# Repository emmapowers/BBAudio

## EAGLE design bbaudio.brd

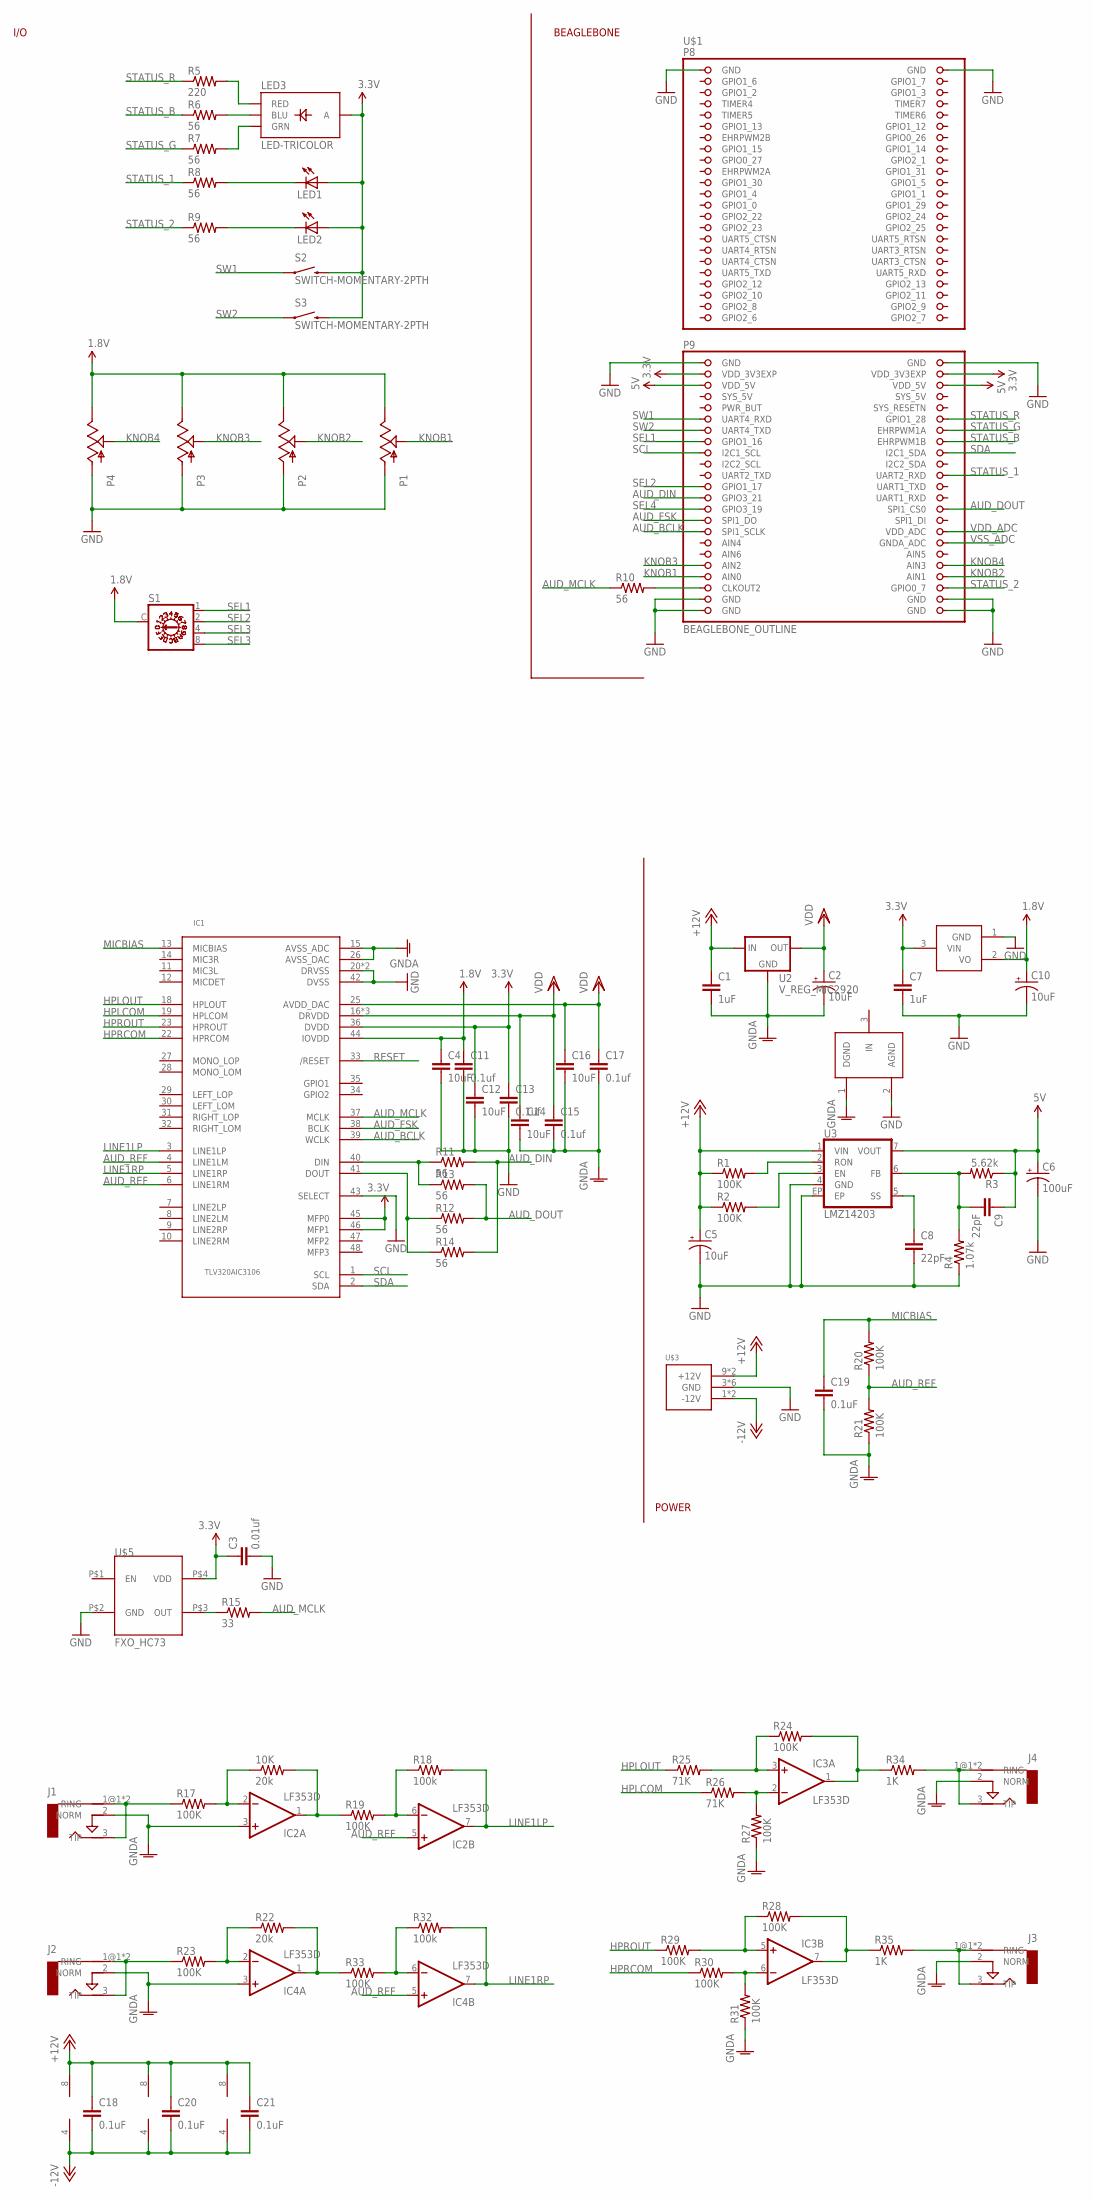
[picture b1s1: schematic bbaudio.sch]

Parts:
10K: 20k; 0603-RES
C1, C7: 1uF; C0603
C2, C5, C10: 10uF; EIA3216
C3: 0.01uf; C0603
C4, C12, C14, C16: 10uF; C0603
C6: 100uF; EIA3216
C8, C9: 22pF; C0603
C11, C13, C15, C17: 0.1uf; C0603
C18, C19, C20, C21: 0.1uF; C0603
IC1: TLV320AIC3106; QFN48
IC2, IC3, IC4: LF353D; SO08
J1, J2, J3, J4: AUDIO-JACKERTHENVAR; ERTHENVAR-JACK
LED1, LED2: LED-FKIT-1206; FKIT-LED-1206
LED3: LED-TRICOLOR; LED-TRICOLOR-SMD
P1, P2, P3, P4: SPARKFUN_POTPDB12; SPARKFUN_PDB12
R1, R2, R17, R19, R20, R21, R23, R24, R27, R28, R29, R30, R31, R33: 100K; 0603-RES
R3: 5.62k; 0603-RES
R4: 1.07k; 0603-RES
R5: 220; 0603-RES
R6, R7, R8, R9, R10, R11, R12, R13, R14: 56; 0603-RES
R15: 33; 0603-RES
R18, R32: 100k; 0603-RES
R22: 20k; 0603-RES
R25, R26: 71K; 0603-RES
R34, R35: 1K; 0603-RES
S1: P103
S2, S3: SWITCH-MOMENTARY-2PTH; TACTILE-PTH
U2: V_REG_MIC2920; SOT223
U3: LMZ14203; TO-PMOD-7
U4: VREG; SOT23-3
U$1: BEAGLEBONE_OUTLINE; BEAGLEBONE_SHIELD
U$3: POWER_SIMPLE10; POWER_10
U$5: FXO_HC73; 4PIN
U$11: GND_CONNECT

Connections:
1.8V: C4.1, C10.A (+), C11.1, IC1.44 (IOVDD), P1.3 (E), P2.3 (E), P3.3 (E), P4.3 (E), S1.C, U4.2 (VO)
3.3V: C3.1, C7.1, C12.1, C13.1, IC1.36 (DVDD), IC1.45 (MFP0), IC1.46 (MFP1), LED1.A, LED2.A, LED3.A, S2.3 (2), S3.3 (2), U4.3 (VIN), U$1.49 (VDD_3V3EXP), U$1.50 (VDD_3V3EXP), U$5.P$4 (VDD)
5V: C6.A (+), C9.1, R3.1, U3.7 (VOUT), U$1.51 (VDD_5V), U$1.52 (VDD_5V)
+12V: C1.1, C5.A (+), C18.1, C20.1, C21.1, IC2.8 (V+), IC3.8 (V+), IC4.8 (V+), R1.1, R2.1, U2.1 (IN), U3.1 (VIN), U$3.9 (+12V), U$3.10 (+12V)
-12V: C18.2, C20.2, C21.2, IC2.4 (V-), IC3.4 (V-), IC4.4 (V-), U$3.1 (-12V), U$3.2 (-12V)
AUD_BCLK: IC1.39 (WCLK), U$1.77 (SPI1_SCLK)
AUD_DIN: R11.2, R14.2, U$1.71 (GPIO3_21)
AUD_DOUT: R12.2, R13.2, U$1.74 (SPI1_CS0)
AUD_FSK: IC1.38 (BCLK), U$1.75 (SPI1_DO)
AUD_MCLK: IC1.37 (MCLK), R10.1, R15.2
AUD_REF: IC1.4 (LINE1LM), IC1.6 (LINE1RM), IC2.5 (+IN), IC4.5 (+IN), R20.1, R21.2
GND: C3.2, C4.2, C5.C (-), C6.C (-), C7.2, C8.2, C10.C (-), C11.2, C12.2, C13.2, IC1.20 (DRVSS), IC1.21 (DRVSS), IC1.42 (DVSS), IC1.43 (SELECT), P1.1 (A), P2.1 (A), P3.1 (A), P4.1 (A), R4.1, U3.4 (GND), U3.EP, U4.1 (GND), U$1.1 (GND), U$1.2 (GND), U$1.47 (GND), U$1.48 (GND), U$1.89 (GND), U$1.90 (GND), U$1.91 (GND), U$1.92 (GND), U$3.3 (GND), U$3.4 (GND), U$3.5 (GND), U$3.6 (GND), U$3.7 (GND), U$3.8 (GND), U$5.P$2 (GND), U$11.2 (AGND)
GNDA: C1.2, C2.C (-), C14.2, C15.2, C16.2, C17.2, C19.2, IC1.15 (AVSS_ADC), IC1.26 (AVSS_DAC), IC2.3 (+IN), IC4.3 (+IN), J1.2 (NORM), J2.2 (NORM), J3.2 (NORM), J4.2 (NORM), R21.1, R27.1, R31.1, U2.2 (GND), U$11.1 (DGND)
HPLCOM: IC1.19 (HPLCOM), R26.1
HPLOUT: IC1.18 (HPLOUT), R25.1
HPRCOM: IC1.22 (HPRCOM), R30.1
HPROUT: IC1.23 (HPROUT), R29.1
KNOB1: P1.2 (S), U$1.85 (AIN0)
KNOB2: P2.2 (S), U$1.86 (AIN1)
KNOB3: P3.2 (S), U$1.83 (AIN2)
KNOB4: P4.2 (S), U$1.84 (AIN3)
LINE1LP: IC1.3 (LINE1LP), IC2.7 (OUT), R18.2
LINE1RP: IC1.5 (LINE1RP), IC4.7 (OUT), R32.2
MICBIAS: C19.1, IC1.13 (MICBIAS), R20.2
unnamed: LED3.R (RED), R5.2
unnamed: LED3.B (BLU), R6.2
unnamed: LED3.G (GRN), R7.2
unnamed: LED1.C, R8.2
unnamed: LED2.C, R9.2
unnamed: R1.2, U3.2 (RON)
unnamed: R2.2, U3.3 (EN)
unnamed: C8.1, U3.5 (SS)
unnamed: R10.2, U$1.87 (CLKOUT2)
unnamed: IC1.40 (DIN), R11.1, R13.1
unnamed: IC1.41 (DOUT), R12.1, R14.1
unnamed: R15.1, U$5.P$3 (OUT)
unnamed: C9.2, R3.2, R4.2, U3.6 (FB)
unnamed: 10K.2, IC2.1 (OUT), R19.1
unnamed: IC2.6 (-IN), R18.1, R19.2
unnamed: 10K.1, IC2.2 (-IN), R17.2
unnamed: J1.1@1 (RING), J1.1@2 (RING), J1.3 (TIP), R17.1
unnamed: J2.1@1 (RING), J2.1@2 (RING), J2.3 (TIP), R23.1
unnamed: J4.1@1 (RING), J4.1@2 (RING), J4.3 (TIP), R34.2
unnamed: IC4.2 (-IN), R22.1, R23.2
unnamed: IC4.1 (OUT), R22.2, R33.1
unnamed: IC4.6 (-IN), R32.1, R33.2
unnamed: IC3.1 (OUT), R24.2, R34.1
unnamed: IC3.3 (+IN), R24.1, R25.2
unnamed: IC3.2 (-IN), R26.2, R27.2
unnamed: IC3.7 (OUT), R28.2, R35.1
unnamed: IC3.5 (+IN), R28.1, R29.2
unnamed: IC3.6 (-IN), R30.2, R31.2
unnamed: J3.1@1 (RING), J3.1@2 (RING), J3.3 (TIP), R35.2
RESET: IC1.33 (/RESET)
SCL: IC1.1 (SCL), U$1.63 (I2C1_SCL)
SDA: IC1.2 (SDA), U$1.64 (I2C1_SDA)
SEL1: S1.1, U$1.61 (GPIO1_16)
SEL2: S1.2, U$1.69 (GPIO1_17)
SEL3: S1.4
SEL4: S1.8, U$1.73 (GPIO3_19)
STATUS_1: R8.1, U$1.68 (UART2_RXD)
STATUS_2: R9.1, U$1.88 (GPIO0_7)
STATUS_B: R6.1, U$1.62 (EHRPWM1B)
STATUS_G: R7.1, U$1.60 (EHRPWM1A)
STATUS_R: R5.1, U$1.58 (GPIO1_28)
SW1: S2.1, U$1.57 (UART4_RXD)
SW2: S3.1, U$1.59 (UART4_TXD)
SYS_5V: U$1.53 (SYS_5V)
VDD: C2.A (+), C14.1, C15.1, C16.1, C17.1, IC1.16 (DRVDD), IC1.17 (DRVDD), IC1.24 (DRVDD), IC1.25 (AVDD_DAC), U2.3 (OUT)
VDD_ADC: U$1.78 (VDD_ADC)
VSS_ADC: U$1.80 (GNDA_ADC)

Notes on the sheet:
I/O
BEAGLEBONE
POWER

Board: 2 copper layers, 81 parts (2 on the bottom side), 66 nets, no tracks yet.

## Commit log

2013-12-13 Some more tewaks to the power section
2013-12-13 Added codec and power connector
2013-12-13 moved some names around
2013-12-14 Added clock source
2013-12-15 Started wiring up the codec
2013-12-15 Added audio i/o
2013-12-16 Moved some stuff around on the board
2013-12-17 Re-did the audio I/O stuff
2013-12-17 Add op-amp power supplies
2013-12-30 More Schematic cleanups
2025-09-25 Add .mailmap to unify author history

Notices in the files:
parts and their libraries:
sparkfun: Licensing: CC v3.0 Share-Alike You are welcome to use this library for commercial purposes.
SparkFun-Aesthetics: Released under the Creative Commons
SparkFun-Aesthetics: http://creativecommons.org/licenses/by-sa/3.0
